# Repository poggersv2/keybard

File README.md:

# keybard (it's not misspelt)

## Overview
**keybard** is a custom mechanical keyboard designed for Hackclub Keeb. Its a modified 60% layout, extended with a dedicated arrow key cluster and a column of macro keys on the side. 

The board is powered by a Raspberry Pi Pico (Orpheus Pico) and uses a sandwich mount case.

## Features
- **Layout:** Modified 60% + Arrow Keys + Macro Column
- **Microcontroller:** Raspberry Pi Pico / Orpheus Pico (RP2040)
- **Mounting Style:** Sandwich Mount
- **Firmware:** RMK with VIA support

## Why I Built It
Standard 60% keyboards are great for desk space but I wanted to have the arrow keys for productivity (and also games).

## What I Learned
Designing and building this board from scratch was kindda difficult: 

### 1. Switch Matrix 
Routing the matrix while making it look decent was hard.

### 2. Tolerances 
When designing the case, I found it hard to imagine the actual size of everything. The maths was a little hard to understand, but that got easier over time.

### 3. CAD
Before this project, I didn't really know how to use Fusion. I had to learn everything from scratch.

## Hardware Details

### Schematic

### PCB

### Case

## Firmware
### How to Compile and Flash
### 1. Get the Firmware
1. Go to the **Actions** tab at the top of this GitHub repository.
2. Click on the latest successful run of the **Build RMK firmware** workflow.
3. Scroll down to the **Artifacts** section at the bottom of the page.
4. Download the compiled firmware `.zip` file and extract it to find your `.uf2` file.

### 2. Flash to the Keyboard
1. Unplug your keyboard.
2. Hold down the **BOOTSEL** button on your Raspberry Pi Pico.
3. While holding the button, plug the keyboard back into your computer via USB. 
4. A new mass storage drive will appear on your computer.
5. Drag and drop the `.uf2` firmware file into this drive.
6. The Pico will automatically reboot, and your keyboard is ready to use!

## Customization
### Keymap Editing (Vial)
This firmware is pre-configured with **Vial** , meaning you can remap your keys, setup macros, and change layers without needing to recompile firmware.

1. Download the Vial app or use the Web UI at [vial.rocks](https://vial.rocks/).
2. Plug in your keyboard and click **Authorize** (if using the web version) or let the app detect it.
3. Remap to your hearts content!

## Credits
* **Hack Club**
* **3D Models:** Cherry MX Switch model from [Thingiverse (2172302)](https://www.thingiverse.com/thing:2172302)
* **Layout Generation:** [Keyboard Tools Editor](https://editor.keyboard-tools.xyz/)
* **Firmware:** [RMK](https://rmk.rs/) and [Vial](https://vial.rocks/)

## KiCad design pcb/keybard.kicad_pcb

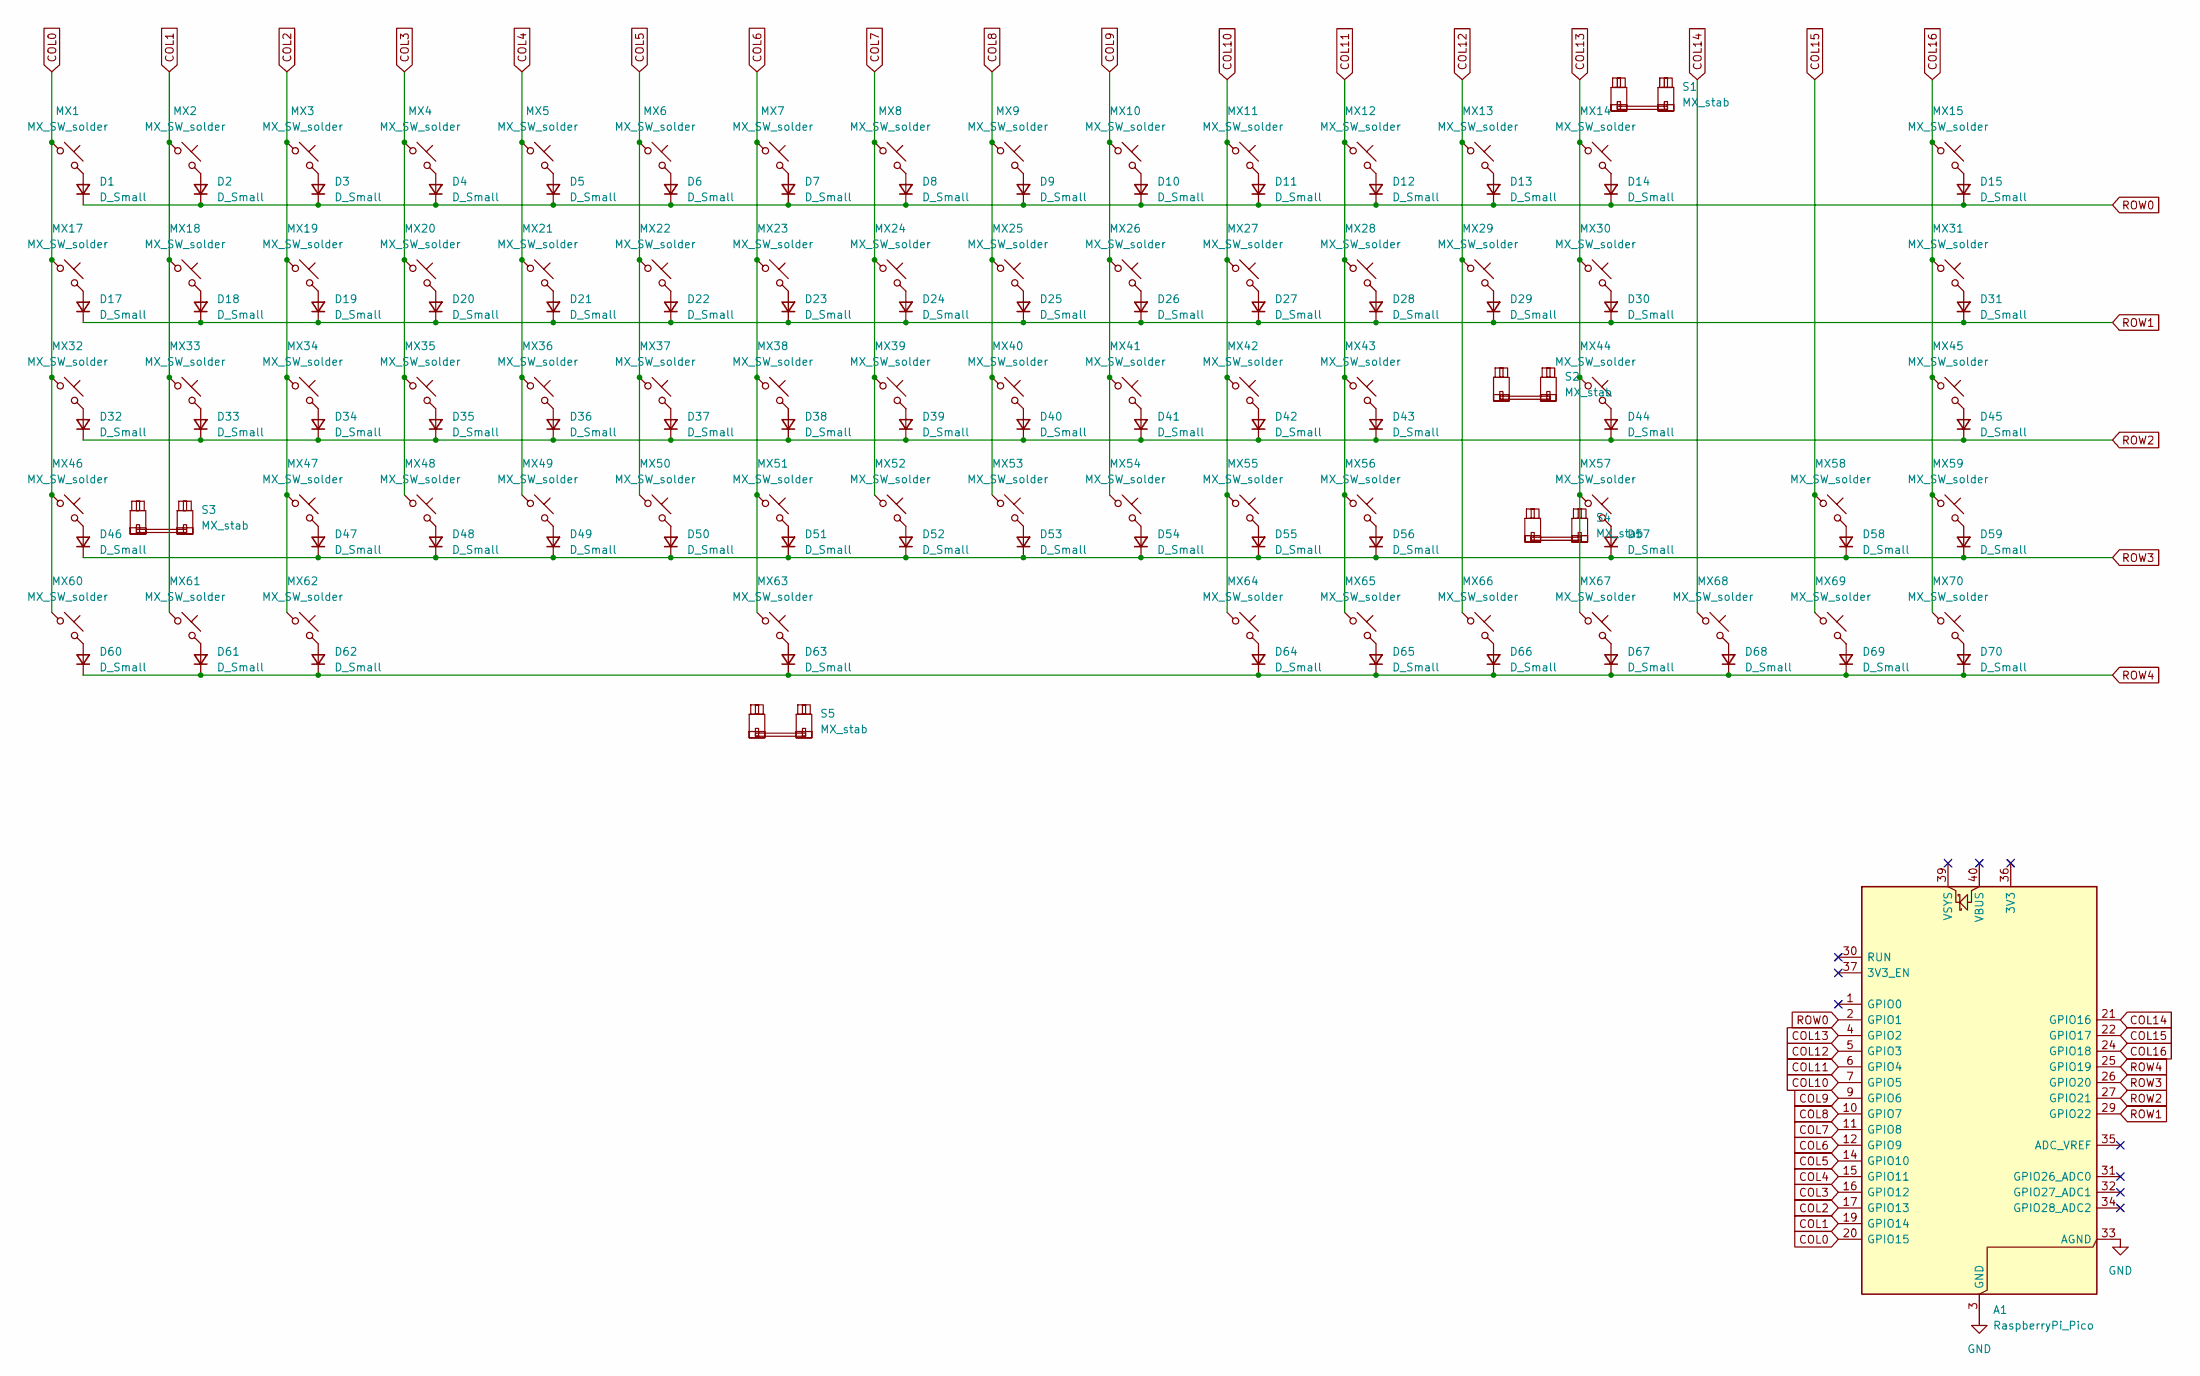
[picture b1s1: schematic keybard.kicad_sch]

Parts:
A1: RaspberryPi_Pico; RaspberryPi_Pico_Common_Unspecified
D1, D2, D3, D4, D5, D6, D7, D8, D9, D10, D11, D12, D13, D14, D15, D17, D18, D19, D20, D21, D22, D23, D24, D25, D26, D27, D28, D29, D30, D31, D32, D33, D34, D35, D36, D37, D38, D39, D40, D41, D42, D43, D44, D45, D46, D47, D48, D49, D50, D51, D52, D53, D54, D55, D56, D57, D58, D59, D60, D61, D62, D63, D64, D65, D66, D67, D68, D69, D70: D_Small; D_DO-35_SOD27_P7.62mm_Horizontal
MX1, MX2, MX3, MX4, MX5, MX6, MX7, MX8, MX9, MX10, MX11, MX12, MX13, MX14, MX15, MX17, MX18, MX19, MX20, MX21, MX22, MX23, MX24, MX25, MX26, MX27, MX28, MX29, MX30, MX31, MX32, MX33, MX34, MX35, MX36, MX37, MX38, MX39, MX40, MX41, MX42, MX43, MX44, MX45, MX46, MX47, MX48, MX49, MX50, MX51, MX52, MX53, MX54, MX55, MX56, MX57, MX58, MX59, MX60, MX61, MX62, MX63, MX64, MX65, MX66, MX67, MX68, MX69, MX70: MX_SW_solder; SW_MX_1u
S1: MX_stab; STAB_MX_2u
S2, S3: MX_stab; STAB_MX_2.25u
S4: MX_stab; STAB_MX_2.75u
S5: MX_stab; STAB_MX_6.25u

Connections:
COL0: A1.20 (GPIO15), MX1.1, MX17.1, MX32.1, MX46.1, MX60.1
COL1: A1.19 (GPIO14), MX2.1, MX18.1, MX33.1, MX61.1
COL2: A1.17 (GPIO13), MX3.1, MX19.1, MX34.1, MX47.1, MX62.1
COL3: A1.16 (GPIO12), MX4.1, MX20.1, MX35.1, MX48.1
COL4: A1.15 (GPIO11), MX5.1, MX21.1, MX36.1, MX49.1
COL5: A1.14 (GPIO10), MX6.1, MX22.1, MX37.1, MX50.1
COL6: A1.12 (GPIO9), MX7.1, MX23.1, MX38.1, MX51.1, MX63.1
COL7: A1.11 (GPIO8), MX8.1, MX24.1, MX39.1, MX52.1
COL8: A1.10 (GPIO7), MX9.1, MX25.1, MX40.1, MX53.1
COL9: A1.9 (GPIO6), MX10.1, MX26.1, MX41.1, MX54.1
COL10: A1.7 (GPIO5), MX11.1, MX27.1, MX42.1, MX55.1, MX64.1
COL11: A1.6 (GPIO4), MX12.1, MX28.1, MX43.1, MX56.1, MX65.1
COL12: A1.5 (GPIO3), MX13.1, MX29.1, MX66.1
COL13: A1.4 (GPIO2), MX14.1, MX30.1, MX44.1, MX57.1, MX67.1
COL14: A1.21 (GPIO16), MX68.1
COL15: A1.22 (GPIO17), MX58.1, MX69.1
COL16: A1.24 (GPIO18), MX15.1, MX31.1, MX45.1, MX59.1, MX70.1
GND: A1.3 (GND), A1.8 (GND), A1.13 (GND), A1.18 (GND), A1.23 (GND), A1.28 (GND), A1.33 (AGND), A1.38 (GND)
unnamed: D1.2 (A), MX1.2
unnamed: D2.2 (A), MX2.2
unnamed: D3.2 (A), MX3.2
unnamed: D4.2 (A), MX4.2
unnamed: D5.2 (A), MX5.2
unnamed: D6.2 (A), MX6.2
unnamed: D7.2 (A), MX7.2
unnamed: D8.2 (A), MX8.2
unnamed: D9.2 (A), MX9.2
unnamed: D10.2 (A), MX10.2
unnamed: D11.2 (A), MX11.2
unnamed: D12.2 (A), MX12.2
unnamed: D13.2 (A), MX13.2
unnamed: D14.2 (A), MX14.2
unnamed: D15.2 (A), MX15.2
unnamed: D17.2 (A), MX17.2
unnamed: D18.2 (A), MX18.2
unnamed: D19.2 (A), MX19.2
unnamed: D20.2 (A), MX20.2
unnamed: D21.2 (A), MX21.2
unnamed: D22.2 (A), MX22.2
unnamed: D23.2 (A), MX23.2
unnamed: D24.2 (A), MX24.2
unnamed: D25.2 (A), MX25.2
unnamed: D26.2 (A), MX26.2
unnamed: D27.2 (A), MX27.2
unnamed: D28.2 (A), MX28.2
unnamed: D29.2 (A), MX29.2
unnamed: D30.2 (A), MX30.2
unnamed: D31.2 (A), MX31.2
unnamed: D32.2 (A), MX32.2
unnamed: D33.2 (A), MX33.2
unnamed: D34.2 (A), MX34.2
unnamed: D35.2 (A), MX35.2
unnamed: D36.2 (A), MX36.2
unnamed: D37.2 (A), MX37.2
unnamed: D38.2 (A), MX38.2
unnamed: D39.2 (A), MX39.2
unnamed: D40.2 (A), MX40.2
unnamed: D41.2 (A), MX41.2
unnamed: D42.2 (A), MX42.2
unnamed: D43.2 (A), MX43.2
unnamed: D44.2 (A), MX44.2
unnamed: D45.2 (A), MX45.2
unnamed: D46.2 (A), MX46.2
unnamed: D47.2 (A), MX47.2
unnamed: D48.2 (A), MX48.2
unnamed: D49.2 (A), MX49.2
unnamed: D50.2 (A), MX50.2
unnamed: D51.2 (A), MX51.2
unnamed: D52.2 (A), MX52.2
unnamed: D53.2 (A), MX53.2
unnamed: D54.2 (A), MX54.2
unnamed: D55.2 (A), MX55.2
unnamed: D56.2 (A), MX56.2
unnamed: D57.2 (A), MX57.2
unnamed: D58.2 (A), MX58.2
unnamed: D59.2 (A), MX59.2
unnamed: D60.2 (A), MX60.2
unnamed: D61.2 (A), MX61.2
unnamed: D62.2 (A), MX62.2
unnamed: D63.2 (A), MX63.2
unnamed: D64.2 (A), MX64.2
unnamed: D65.2 (A), MX65.2
unnamed: D66.2 (A), MX66.2
unnamed: D67.2 (A), MX67.2
unnamed: D68.2 (A), MX68.2
unnamed: D69.2 (A), MX69.2
unnamed: D70.2 (A), MX70.2
ROW0: A1.2 (GPIO1), D1.1 (K), D2.1 (K), D3.1 (K), D4.1 (K), D5.1 (K), D6.1 (K), D7.1 (K), D8.1 (K), D9.1 (K), D10.1 (K), D11.1 (K), D12.1 (K), D13.1 (K), D14.1 (K), D15.1 (K)
ROW1: A1.29 (GPIO22), D17.1 (K), D18.1 (K), D19.1 (K), D20.1 (K), D21.1 (K), D22.1 (K), D23.1 (K), D24.1 (K), D25.1 (K), D26.1 (K), D27.1 (K), D28.1 (K), D29.1 (K), D30.1 (K), D31.1 (K)
ROW2: A1.27 (GPIO21), D32.1 (K), D33.1 (K), D34.1 (K), D35.1 (K), D36.1 (K), D37.1 (K), D38.1 (K), D39.1 (K), D40.1 (K), D41.1 (K), D42.1 (K), D43.1 (K), D44.1 (K), D45.1 (K)
ROW3: A1.26 (GPIO20), D46.1 (K), D47.1 (K), D48.1 (K), D49.1 (K), D50.1 (K), D51.1 (K), D52.1 (K), D53.1 (K), D54.1 (K), D55.1 (K), D56.1 (K), D57.1 (K), D58.1 (K), D59.1 (K)
ROW4: A1.25 (GPIO19), D60.1 (K), D61.1 (K), D62.1 (K), D63.1 (K), D64.1 (K), D65.1 (K), D66.1 (K), D67.1 (K), D68.1 (K), D69.1 (K), D70.1 (K)

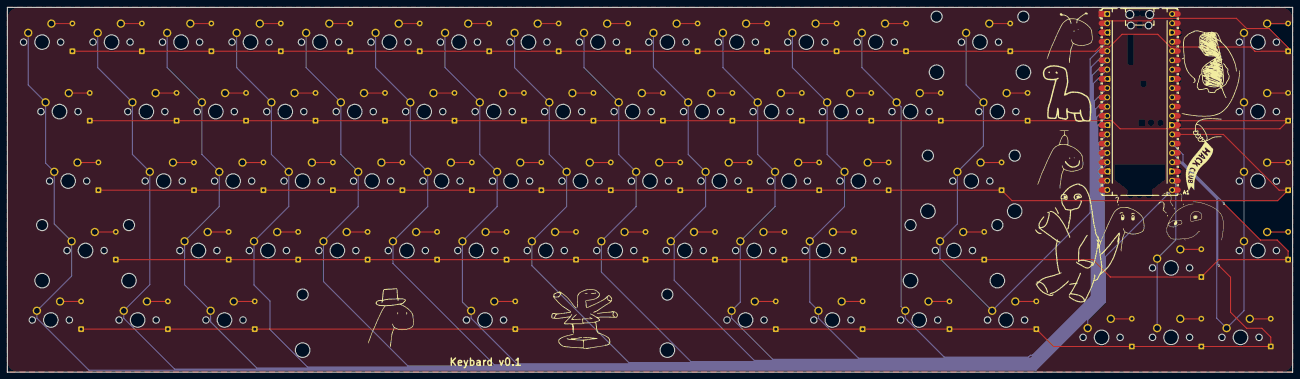
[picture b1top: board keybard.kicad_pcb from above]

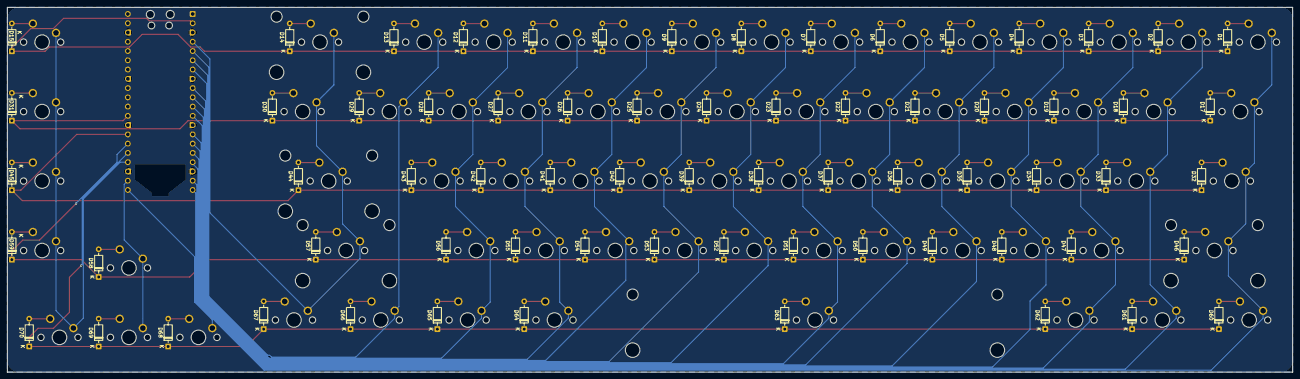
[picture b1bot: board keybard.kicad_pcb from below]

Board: 2 copper layers, 352.4 x 100.0 mm, 144 parts (69 on the bottom side), 92 nets.
